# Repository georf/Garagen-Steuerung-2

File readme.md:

# Garagen-Tool 2

Weitere Informationen: https://georf.de/1493/garagen-tools-2/

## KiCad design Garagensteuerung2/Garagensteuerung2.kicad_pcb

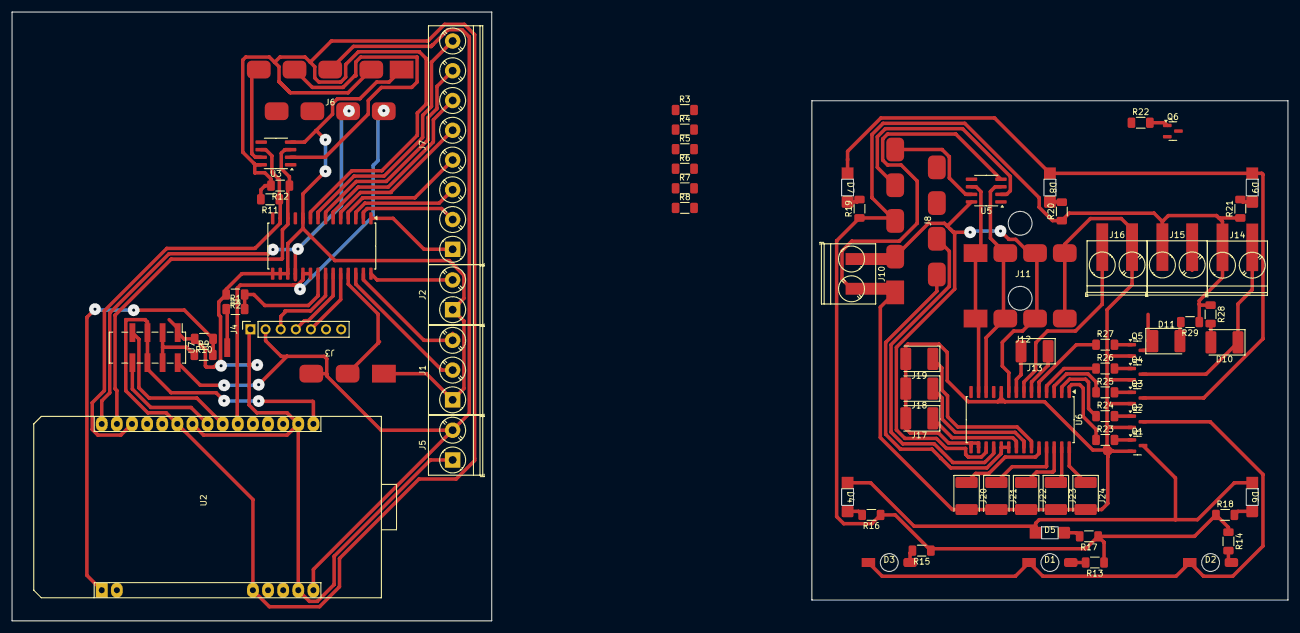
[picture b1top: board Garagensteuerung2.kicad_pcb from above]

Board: 2 copper layers, 214.4 x 102.3 mm, 75 parts (0 on the bottom side), 78 nets.

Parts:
D1, D2, D3: LED_Status1; LED 3mm mit Loch
D4, D5, D6, D7, D8, D9: LED_Status1; LED SMD mit Loch
D10, D11: LED_Status1; D_2114_3652Metric_Pad1.85x3.75mm_HandSolder
J1: Conn_LidEnd; TerminalBlock_Phoenix_PT-1,5-3-5.0-H_1x03_P5.00mm_Horizontal
J2: Conn_DoorBack; TerminalBlock_Phoenix_PT-1,5-2-5.0-H_1x02_P5.00mm_Horizontal
J3: Conn_Motion; 3 SMD Pins
J4: Conn_Radio; PinSocket_1x07_P2.54mm_Vertical
J5: Conn_Voltage; TerminalBlock_Phoenix_PT-1,5-2-5.0-H_1x02_P5.00mm_Horizontal
J6: Conn_D-Sub-Backend; D-Sub female
J7: Conn_Relais; TerminalBlock_Phoenix_PT-1,5-8-5.0-H_1x08_P5.00mm_Horizontal
J8: Conn_D-Sub-Handheld; D-Sub male
J10: Conn_Temp; TerminalBlock_Umgebogen-2x5mm
J11: OLED Oben; 4 SMD Pins
J12: OLED Unten; 4 SMD Pins
J13: Jumper; D_2114_3652Metric_Pad1.85x3.75mm_HandSolder
J14: Conn_Gate; TerminalBlock_Umgebogen-2x5mm
J15: Conn_LedLid; TerminalBlock_Umgebogen-2x5mm
J16: Conn_DoorFront; TerminalBlock_Umgebogen-2x5mm
J17: Conn_BtnLight; D_2114_3652Metric_Pad1.85x3.75mm_HandSolder
J18: Conn_BtnGate; D_2114_3652Metric_Pad1.85x3.75mm_HandSolder
J19: Conn_BtnLid; D_2114_3652Metric_Pad1.85x3.75mm_HandSolder
J20: Conn_BtnUp; D_2114_3652Metric_Pad1.85x3.75mm_HandSolder
J21: Conn_BtnRight; D_2114_3652Metric_Pad1.85x3.75mm_HandSolder
J22: Conn_BtnDown; D_2114_3652Metric_Pad1.85x3.75mm_HandSolder
J23: Conn_BtnLeft; D_2114_3652Metric_Pad1.85x3.75mm_HandSolder
J24: Conn_BtnOkay; D_2114_3652Metric_Pad1.85x3.75mm_HandSolder
Q1, Q2, Q3, Q4, Q5, Q6: MMBT3904; SOT-23
R1: 75k; R_1206_3216Metric_Pad1.30x1.75mm_HandSolder
R2: 15k; R_1206_3216Metric_Pad1.30x1.75mm_HandSolder
R3, R4, R11, R12: 4k7; R_1206_3216Metric_Pad1.30x1.75mm_HandSolder
R5, R6, R7, R8: 470; R_1206_3216Metric_Pad1.30x1.75mm_HandSolder
R9, R10: 0; R_1206_3216Metric_Pad1.30x1.75mm_HandSolder
R13, R14, R15, R16, R17, R18, R19, R20, R21, R28, R29: 100; R_1206_3216Metric_Pad1.30x1.75mm_HandSolder
R22, R23, R24, R25, R26, R27: 2k2; R_1206_3216Metric_Pad1.30x1.75mm_HandSolder
U2: NodeMCU ESP8266 weniger Pins
U3, U5: P82B715DR; SOIC-8_3.9x4.9mm_P1.27mm
U4, U6: MCP23017_SO; SOIC-28W_7.5x17.9mm_P1.27mm
U7: PinHeader_2x05_SMD Mit Pad 9

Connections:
24V-Detector: R1.2, R2.1, U4.21 (GPA0)
+3.3V: J6.2, R7.1, R8.1, R11.2, R12.2, U2.11 (3V3), U2.16 (3V3), U2.25 (3V3), U3.8 (VCC), U4.9 (VDD), U7.5 (L_EN), U7.6 (R_EN)
+3.3VA: J8.2, J10.1, J11.3, J12.3, R3.2, R4.2, R5.1, R6.1, U5.8 (VCC), U6.9 (VDD), U6.17 (A2)
+5V: J3.3, J4.2, J5.2, J6.3, U2.15 (Vin), U7.2 (VCC)
+5VA: J8.3, J14.1, J15.1, R13.1, R14.1, R15.1, R16.1, R17.1, R18.1, R19.1, R20.1, R21.1, R28.1, R29.1
Current: R9.2, R10.1, U2.1 (A0)
D5: U2.23 (D5), U7.8 (R_PWM)
D6: U2.22 (D6), U7.7 (L_PWM)
DoorBack: J2.2, U4.28 (GPA7)
GND: J1.1, J2.1, J3.1, J4.1, J5.1, J6.1, R2.2, R10.2, U2.14 (GND), U2.17 (GND), U2.24 (GND), U3.4 (GND), U4.10 (VSS), U4.15 (A0), U4.16 (A1), U4.17 (A2), U7.1 (GND)
GND1: J8.1, J10.2, J11.4, J12.4, J16.2, J17.2, J18.2, J19.2, J20.2, J21.2, J22.2, J23.2, J24.2, Q1.2 (E), Q2.2 (E), Q3.2 (E), Q4.2 (E), Q5.2 (E), Q6.2 (E), U5.4 (GND), U6.10 (VSS), U6.15 (A0), U6.16 (A1)
LedBtns: D7.1 (K), D8.1 (K), D9.1 (K), Q3.3 (C)
LedChargeHeavy: D4.1 (K), D5.1 (K), D6.1 (K), Q1.3 (C)
LedChargeLight: D1.1 (K), D2.1 (K), D3.1 (K), Q2.3 (C)
LedGate: D10.1 (K), J14.2, Q4.3 (C)
LedLid: D11.1 (K), Q5.3 (C)
LidEndDown: J1.3, U4.27 (GPA6)
LidEndUp: J1.2, U4.26 (GPA5)
Motion: J3.2, U4.25 (GPA4)
unnamed: D1.2 (A), R13.2
unnamed: D2.2 (A), R14.2
unnamed: D3.2 (A), R15.2
unnamed: D4.2 (A), R16.2
unnamed: D5.2 (A), R17.2
unnamed: D6.2 (A), R18.2
unnamed: D7.2 (A), R19.2
unnamed: D8.2 (A), R20.2
unnamed: D9.2 (A), R21.2
unnamed: D10.2 (A), R28.2
unnamed: D11.2 (A), R29.2
unnamed: J6.4, R8.2, U3.2 (LX)
unnamed: J6.5, R7.2, U3.7 (LY)
unnamed: J6.6, U2.21 (D7), U4.19 (INTB), U4.20 (INTA)
unnamed: J6.7, U2.30 (D0), U4.18 (~RESET)
unnamed: J7.1, U4.1 (GPB0)
unnamed: J7.2, U4.2 (GPB1)
unnamed: J7.3, U4.3 (GPB2)
unnamed: J7.4, U4.4 (GPB3)
unnamed: J7.5, U4.5 (GPB4)
unnamed: J7.6, U4.6 (GPB5)
unnamed: J7.7, U4.7 (GPB6)
unnamed: J7.8, U4.8 (GPB7)
unnamed: J8.4, R5.2, U5.2 (LX)
unnamed: J8.5, R6.2, U5.7 (LY)
unnamed: J8.6, U6.19 (INTB), U6.20 (INTA)
unnamed: J8.7, U6.18 (~RESET)
unnamed: J11.1, J12.1, R4.1, U5.6 (SY), U6.13 (SDA)
unnamed: J11.2, J12.2, R3.1, U5.3 (SX), U6.12 (SCK)
unnamed: J13.1, U6.6 (GPB5)
unnamed: J15.2, Q6.3 (C)
unnamed: J16.1, U6.7 (GPB6)
unnamed: J17.1, U6.21 (GPA0)
unnamed: J18.1, U6.22 (GPA1)
unnamed: J19.1, U6.23 (GPA2)
unnamed: J20.1, U6.24 (GPA3)
unnamed: J21.1, U6.25 (GPA4)
unnamed: J22.1, U6.26 (GPA5)
unnamed: J23.1, U6.27 (GPA6)
unnamed: J24.1, U6.28 (GPA7)
unnamed: Q1.1 (B), R23.2
unnamed: Q2.1 (B), R24.2
unnamed: Q3.1 (B), R25.2
unnamed: Q4.1 (B), R26.2
unnamed: Q5.1 (B), R27.2
unnamed: Q6.1 (B), R22.2
unnamed: R12.1, U2.29 (D1), U3.3 (SX), U4.12 (SCK)
unnamed: R11.1, U2.28 (D2), U3.6 (SY), U4.13 (SDA)
unnamed: R23.1, U6.1 (GPB0)
unnamed: R24.1, U6.2 (GPB1)
unnamed: R25.1, U6.3 (GPB2)
unnamed: R26.1, U6.4 (GPB3)
unnamed: R27.1, U6.5 (GPB4)
unnamed: R22.1, U6.8 (GPB7)
unnamed: R1.1, U7.9 (B+)
unnamed: R9.1, U7.3 (L_IS), U7.4 (R_IS)
Radio0: J4.3, U4.22 (GPA1)
Radio1: J4.4, U4.23 (GPA2)
Radio2: J4.5, U4.24 (GPA3)

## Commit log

2025-12-23 3D-Modelle
2025-12-23 Software im Stand vom Blog-Post
2025-12-23 Ignoriere Cache, Backups und Bilder
2025-12-23 Kicad-Projekt
2025-12-23 Readme ergänzen
2026-01-27 Motor-Netzteil für Batterie-Notladung verwenden
2026-01-27 Licht bei Torbewegung automatisch anschalten
2026-01-27 Hoftor-Steuerung korrigieren
2026-01-27 Restart-Button für HA verteilen
2026-01-27 Maximaler PWM-Wert korrigieren
2026-02-08 Ausgewählte Logs per MQTT senden
2026-02-08 Schwellwerte anpassen
2026-02-08 LED Lid bei offenen Zustand anschalten
2026-02-08 Wenn genau 0 Watt, auch umschalten
2026-02-08 alle 2 Tage neustarten
2026-02-26 Netz-Power zusammenrechnen
2026-02-26 LED Lid bei offenen Zustand ausschalten
2026-03-11 Bewegung des Tores über MQTT verteilen
2026-04-06 Code verbessern
    - Debug-Build ermöglichen
    - ChargeConfig in Klasse auslagern
    - MCP-Fehlerkorrektur
    - Relais-Sondersteuerung für Laden verbessern
    - Timer auslagern und Overflow korrigieren
    - Zusätzliche LED ansteuern
2026-04-06 Verbesserungen in der Platine einarbeiten
